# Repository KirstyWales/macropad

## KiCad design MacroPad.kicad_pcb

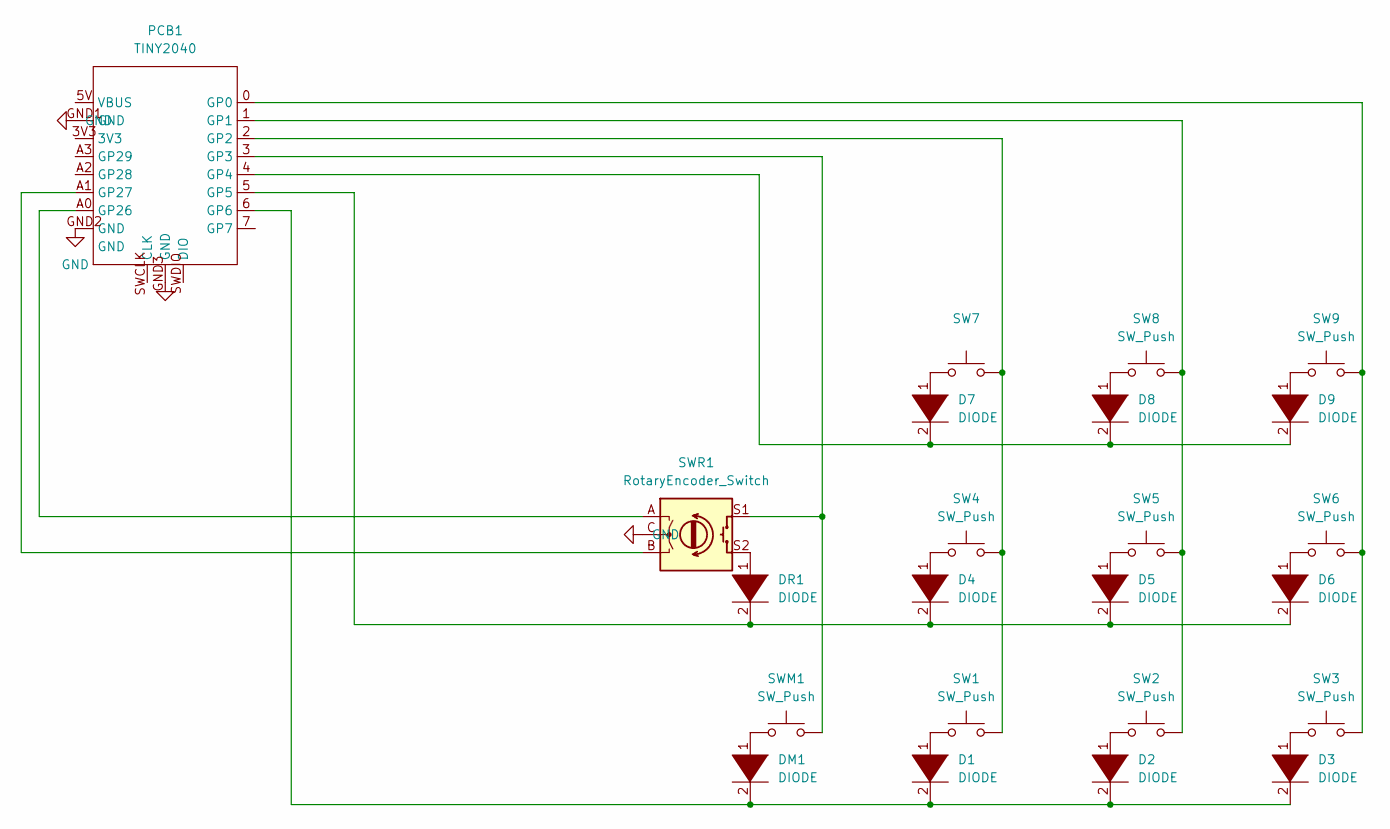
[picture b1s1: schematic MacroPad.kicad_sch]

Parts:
D1, D2, D3, D4, D5, D6, D7, D8, D9: DIODE; D_SOD-123
DM1: DIODE; D_SOD-123
DR1: DIODE; D_SOD-123
PCB1: TINY2040
SW1, SW2, SW3, SW4, SW5, SW6, SW8, SW9: SW_Push
SW7: (no value)
SWM1: SW_Push
SWR1: RotaryEncoder_Switch; RotaryEncoder_Alps_EC11E-Switch_Vertical_H20mm

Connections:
GND: PCB1.GND1 (GND), PCB1.GND2 (GND), PCB1.GND3 (GND), SWR1.C
unnamed: D1.1 (K), SW1.1
unnamed: D1.2 (A), D2.2 (A), D3.2 (A), DM1.2 (A), PCB1.6 (GP6)
unnamed: D2.1 (K), SW2.1
unnamed: D3.1 (K), SW3.1
unnamed: D4.1 (K), SW4.1
unnamed: D4.2 (A), D5.2 (A), D6.2 (A), DR1.2 (A), PCB1.5 (GP5)
unnamed: D5.1 (K), SW5.1
unnamed: D6.1 (K), SW6.1
unnamed: D7.1 (K), SW7.1
unnamed: D7.2 (A), D8.2 (A), D9.2 (A), PCB1.4 (GP4)
unnamed: D8.1 (K), SW8.1
unnamed: D9.1 (K), SW9.1
unnamed: DM1.1 (K), SWM1.1
unnamed: DR1.1 (K), SWR1.S2
unnamed: PCB1.0 (GP0), SW3.2, SW6.2, SW9.2
unnamed: PCB1.1 (GP1), SW2.2, SW5.2, SW8.2
unnamed: PCB1.2 (GP2), SW1.2, SW4.2, SW7.2
unnamed: PCB1.3 (GP3), SWM1.2, SWR1.S1
unnamed: PCB1.A0 (GP26), SWR1.A
unnamed: PCB1.A1 (GP27), SWR1.B

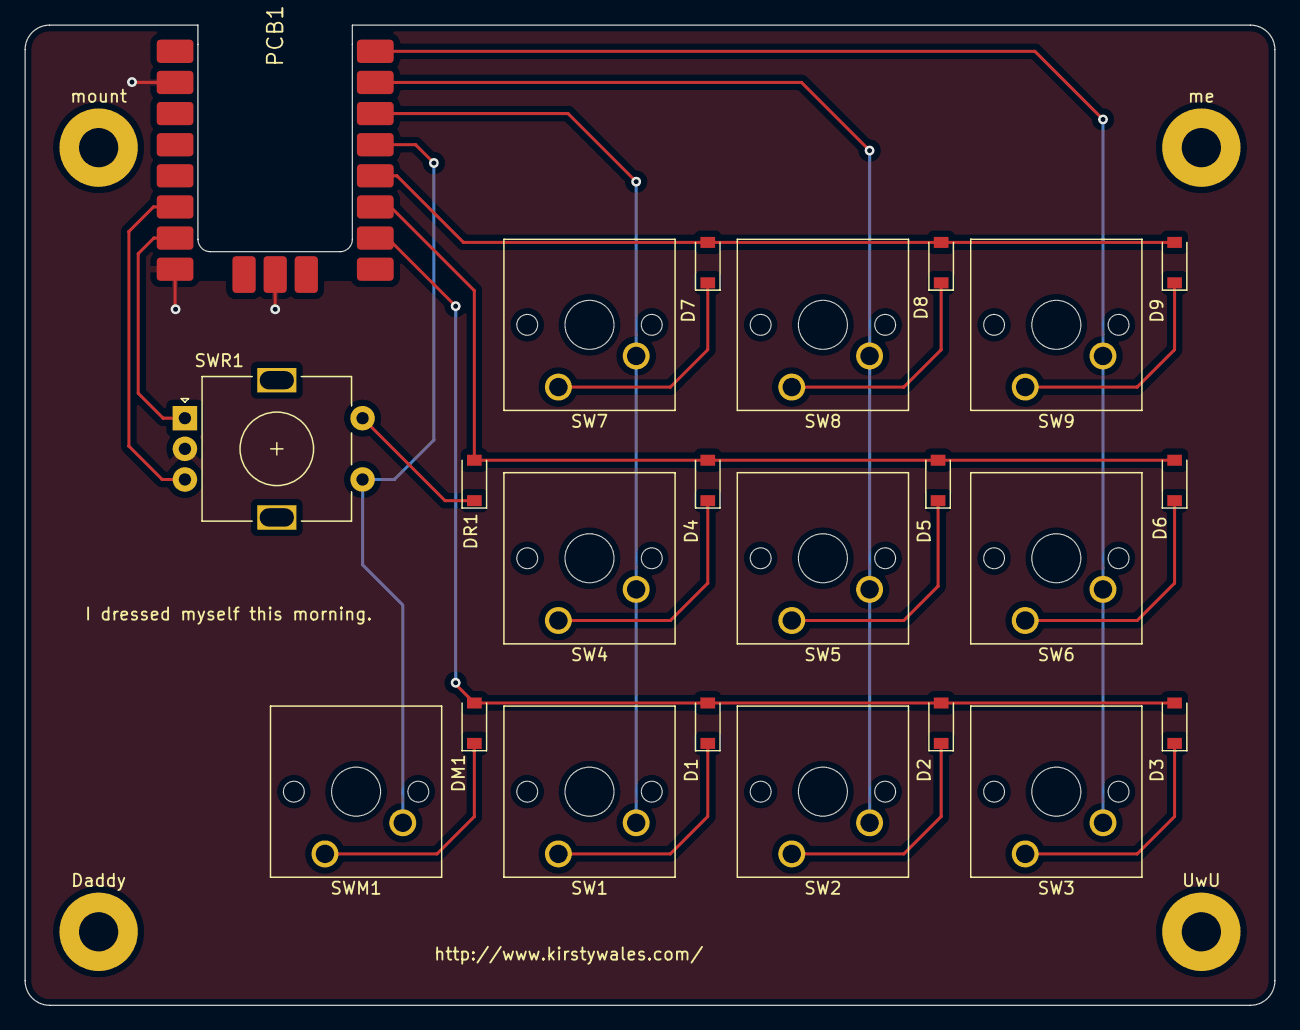
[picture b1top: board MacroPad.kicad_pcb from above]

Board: 2 copper layers, 102.0 x 80.0 mm, 27 parts (0 on the bottom side), 21 nets.

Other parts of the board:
Daddy: MountingHole_3.2mm_M3_Pad
UwU: MountingHole_3.2mm_M3_Pad
me: MountingHole_3.2mm_M3_Pad
mount: MountingHole_3.2mm_M3_Pad

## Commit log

2022-05-18 added files via upload
    revision 1
